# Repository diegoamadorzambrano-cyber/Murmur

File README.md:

# Murmur
An AI powered device that holds recording as your second brain.

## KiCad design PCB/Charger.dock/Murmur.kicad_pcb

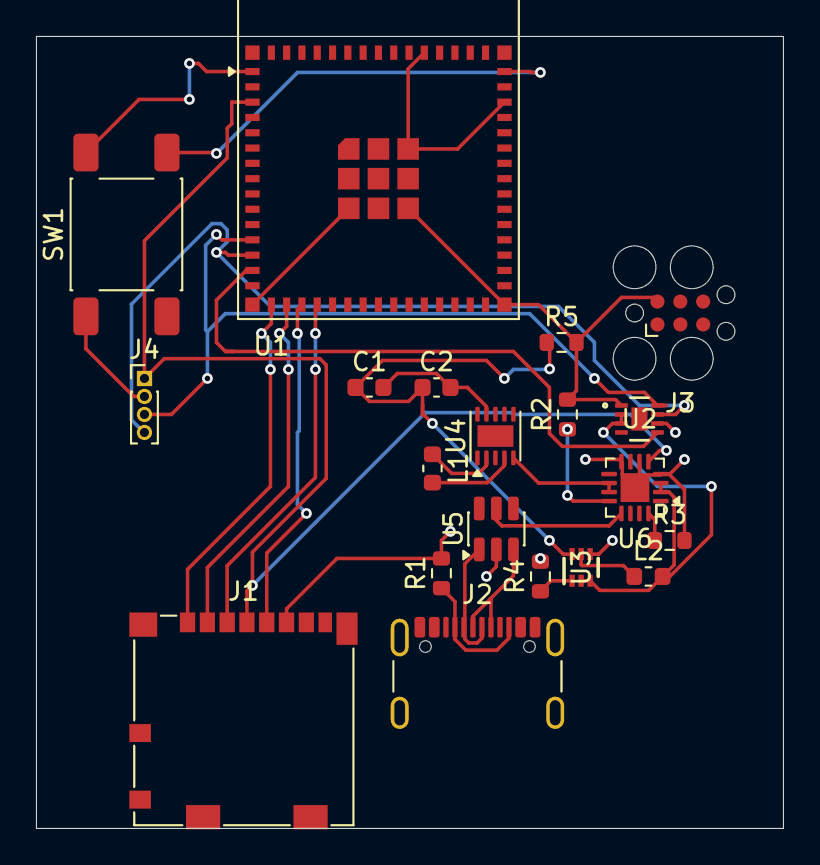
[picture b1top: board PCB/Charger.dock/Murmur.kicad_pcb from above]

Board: 2 copper layers, 41.5 x 44.0 mm, 20 parts (0 on the bottom side), 25 nets.

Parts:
C1, C2: 22nf; C_0603_1608Metric
J1: Molex 104031-0811; microSD_HC_Molex_104031-0811
J2: USB4105-GF-A; USB_C_Receptacle_GCT_USB4105-xx-A_16P_TopMnt_Horizontal
J3: Conn_01x04_Pin; Tag-Connect_TC2030-IDC-FP_2x03_P1.27mm_Vertical
J4: I2C OLED; PinHeader_1x04_P1.00mm_Vertical
L1: 1.5nh; L_0603_1608Metric
L2: 1nh; L_0603_1608Metric
R1: 5.1kOhm; R_0603_1608Metric
R2: 1.5kOhm; R_0603_1608Metric
R3: 1.78kOhm; R_0603_1608Metric
R4: 100kOhm; R_0603_1608Metric
R5: 732kOhm; R_0603_1608Metric
SW1: SW_Push; SW_Push_1P1T_NO_E-Switch_TL3301NxxxxxG
U1: ESP32-S3-MINI-1; ESP32-S2-MINI-1
U2: MAX17048G+T10; 21-0168E_T822-3_MXM
U3: TPS61023DRLR; DRL0006A
U4: TPS63031DSK; WSON-10-1EP_2.5x2.5mm_P0.5mm_EP1.2x2mm
U5: USBLC6-2SC6; SOT-23-6
U6: BQ24074RGT; VQFN-16-1EP_3x3mm_P0.5mm_EP1.6x1.6mm

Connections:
+3.3V: J1.4 (VDD), J4.1, U1.3 (3V3), U4.1 (VOUT), U4.6 (EN), U6.5 (EN2)
+5V: C1.1, C2.1, R5.1, U3.6 (VOUT)
+BATT: L2.2, U2.2 (CELL), U2.3 (VDD), U3.2 (EN), U3.3 (VIN), U6.2 (BAT), U6.3 (BAT)
-BATT: C1.2, C2.2, J1.6 (VSS), J3.2, J4.2, R1.2, R2.2, R3.2, R4.2, R5.2, SW1.1, U1.1 (GND), U1.2 (GND), U1.42 (GND), U1.43 (GND), U1.46 (GND), U1.47 (GND), U1.48 (GND), U1.49 (GND), U1.50 (GND), U1.51 (GND), U1.52 (GND), U1.53 (GND), U1.54 (GND), U1.55 (GND), U1.56 (GND), U1.57 (GND), U1.58 (GND), U1.59 (GND), U1.60 (GND), U1.61 (GND), U1.62 (GND), U1.63 (GND), U1.64 (GND), U1.65 (GND), U2.1 (CTG), U2.4 (GND), U2.6 (QSTRT), U3.4 (GND), U4.7 (PS/SYNC), U4.9 (GND), U5.2 (GND), U6.4 (~CE), U6.6 (EN1), U6.8 (VSS), U6.17 (VSS)
/CC: J2.A5 (CC1), J2.B5 (CC2), R1.1
/DN: J2.A7 (DN1), J2.B7 (DN2), U5.1 (I/O1)
/DP: J2.A6 (DP1), J2.B6 (DP2), U5.3 (I/O2)
/ILIM: R2.1, U6.12 (ILIM)
/IO8: J4.3, U1.12 (IO8), U2.8 (SDA)
/IO9: J4.4, U1.13 (IO9), U2.7 (SCL)
/IO10: U1.6 (IO2), U1.14 (IO10), U2.5 (*ALRT)
/IO12: J1.1 (DAT2), U1.16 (IO12)
/IO13: J1.2 (CD/DAT3), U1.17 (IO13)
/IO14: J1.5 (CLK), U1.18 (IO14)
/IO15: J1.3 (CMD), U1.19 (IO15)
/IO19: U1.39 (TXD0), U5.4 (I/O2)
/IO20: U1.40 (RXD0), U5.6 (I/O1)
/ISET: R3.1, U6.16 (ISET)
/OUT: U4.5 (VIN), U6.10 (OUT), U6.11 (OUT)
/VBUS: U5.5 (VBUS), U6.13 (IN)
unnamed: SW1.2, U1.45 (EN)
unnamed: R4.1, U3.1 (FB)
unnamed: L2.1, U3.5 (SW)
unnamed: L1.2, U4.4 (L1)
unnamed: L1.1, U4.2 (L2)

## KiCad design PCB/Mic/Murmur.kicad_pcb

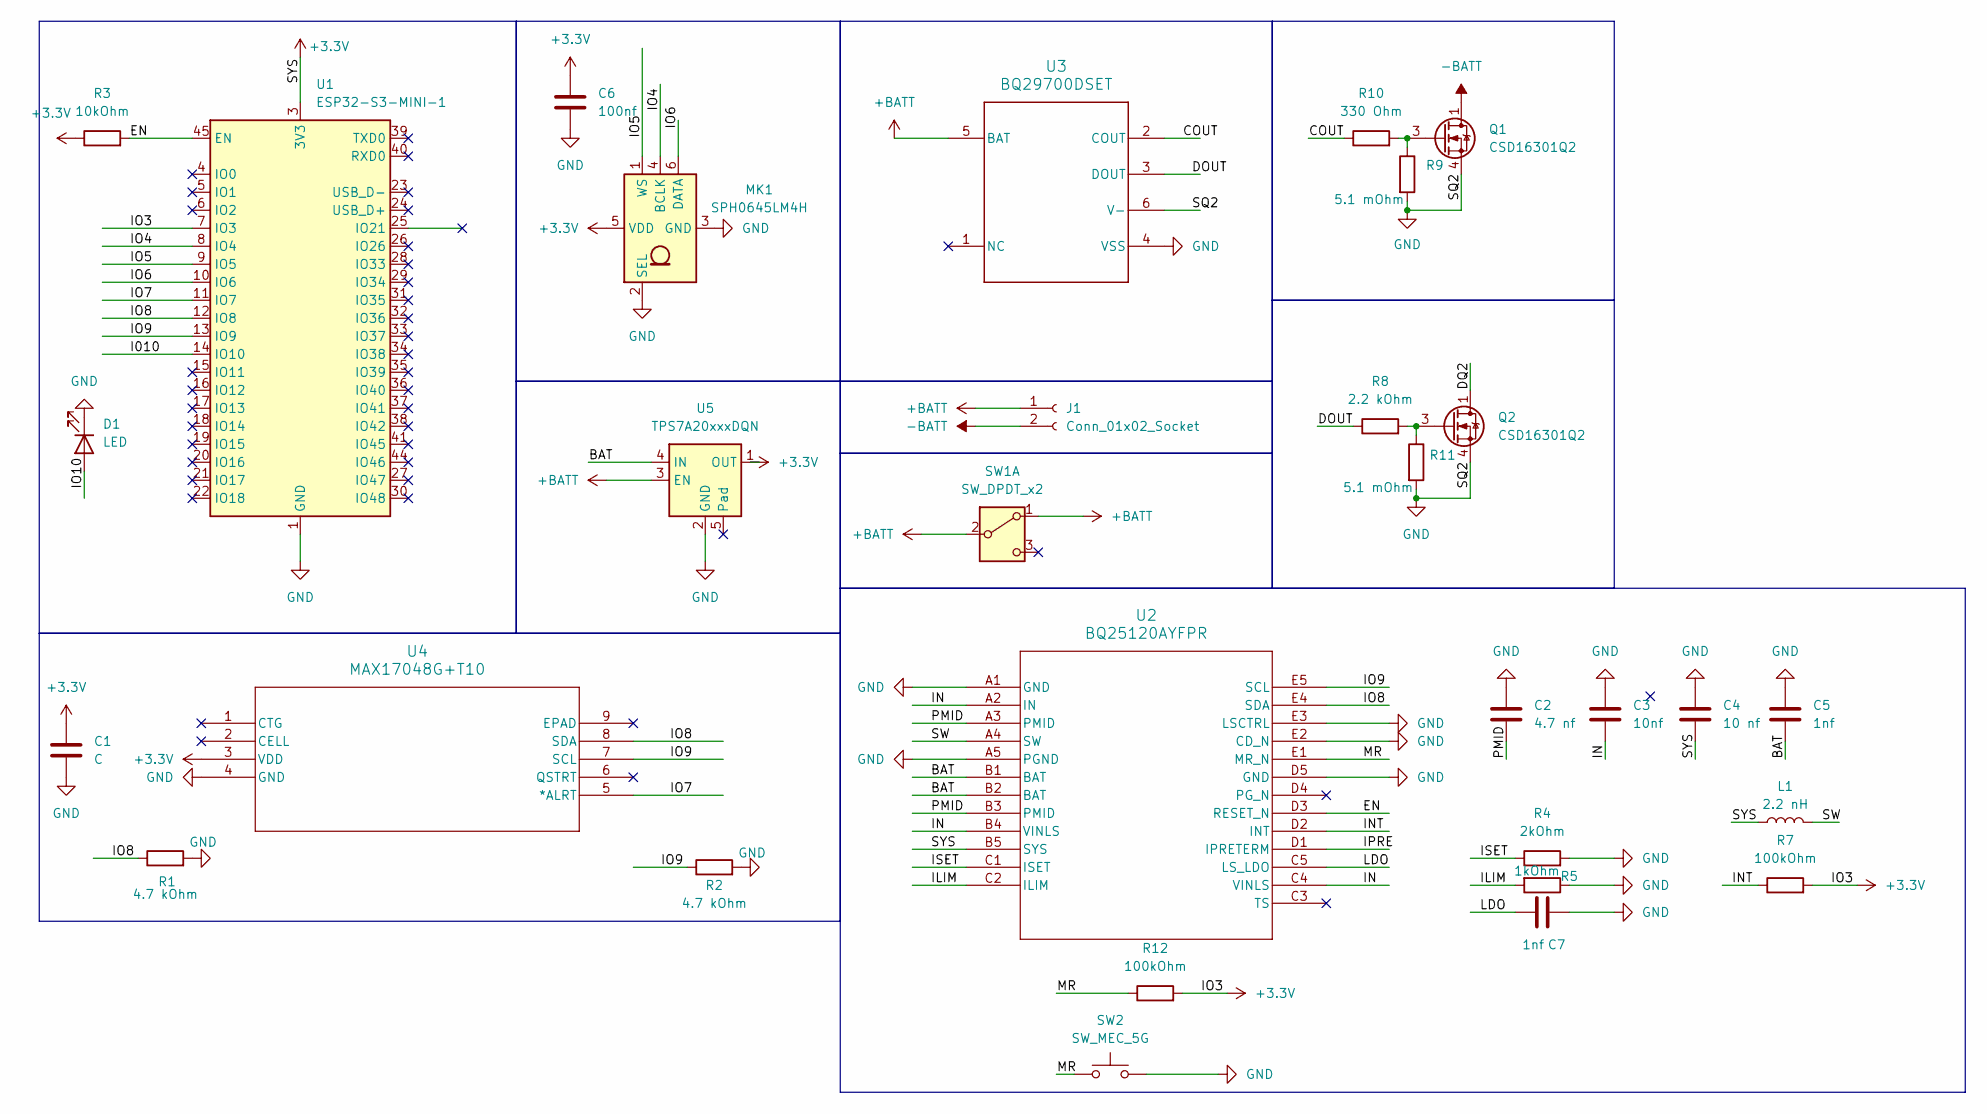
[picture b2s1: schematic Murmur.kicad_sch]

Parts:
C1: C; C_0603_1608Metric
C2: 4.7 nf; C_0603_1608Metric
C3: 10nf; C_0603_1608Metric
C4: 10 nf; C_0603_1608Metric
C5, C7: 1nf; C_0603_1608Metric
C6: 100nf; C_0603_1608Metric
D1: LED; Texas_DQK
J1: Conn_01x02_Socket; Tag-Connect_TC2030-IDC-FP_2x03_P1.27mm_Vertical
L1: 2.2 nH; L_0402_1005Metric
MK1: SPH0645LM4H; Knowles_SPH0645LM4H-6_3.5x2.65mm
Q1, Q2: CSD16301Q2; Texas_DQK
R1, R2: 4.7 kOhm; R_0603_1608Metric
R3: 10kOhm; R_0603_1608Metric
R4: 2kOhm; R_0603_1608Metric
R5: 1kOhm; R_0603_1608Metric
R7, R12: 100kOhm; R_0603_1608Metric
R8: 2.2 kOhm; R_0603_1608Metric
R9, R11: 5.1 mOhm; R_0603_1608Metric
R10: 330 Ohm; R_0603_1608Metric
SW1: SW_DPDT_x2; SW_PUSH_1P1T_6x3.5mm_H5.0_APEM_MJTP1250
SW2: SW_MEC_5G; SW_Push_SPST_NO_Alps_SKRK
U1: ESP32-S3-MINI-1; ESP32-S2-MINI-1
U2: BQ25120AYFPR; YFP0025BABD_TEX
U3: BQ29700DSET; DSE0006A
U4: MAX17048G+T10; 21-0168E_T822-3_MXM
U5: TPS7A20xxxDQN; Texas_X2SON-4_1x1mm_P0.65mm

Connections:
+3.3V: C1.1, C4.2, C6.1, L1.1, MK1.5 (VDD), R3.1, R7.2, R12.2, U1.3 (3V3), U1.7 (IO3), U2.B5 (SYS), U4.3 (VDD), U5.1 (OUT)
+BATT: J1.1, SW1.1 (A), SW1.2 (B), U3.5 (BAT), U5.3 (EN)
-BATT: J1.2, Q1.1 (D), Q1.2 (D), Q1.5 (D), Q1.6 (D), Q1.8 (D)
/BAT: C5.2, U2.B1 (BAT), U2.B2 (BAT), U5.4 (IN)
/COUT: R10.1, U3.2 (COUT)
/DOUT: R8.1, U3.3 (DOUT)
/DQ2: Q2.1 (D), Q2.2 (D), Q2.5 (D), Q2.6 (D), Q2.8 (D)
/EN: R3.2, U1.45 (EN), U2.D3 (RESET_N)
/I010: U1.14 (IO10)
/ILIM: R5.2, U2.C2 (ILIM)
/IN: C3.2, U2.A2 (IN), U2.B4 (VINLS), U2.C4 (VINLS)
/INT: R7.1, U2.D2 (INT)
/IO4: MK1.4 (BCLK), U1.8 (IO4)
/IO5: MK1.1 (WS), U1.9 (IO5)
/IO6: MK1.6 (DATA), U1.10 (IO6)
/IO7: U1.11 (IO7), U4.5 (*ALRT)
/IO8: R1.1, U1.12 (IO8), U2.E4 (SDA), U4.8 (SDA)
/IO9: R2.1, U1.13 (IO9), U2.E5 (SCL), U4.7 (SCL)
/IO10: D1.2 (A)
/IPRE: U2.D1 (IPRETERM)
/ISET: R4.1, U2.C1 (ISET)
/LDO: C7.1, U2.C5 (LS_LDO)
/MR: R12.1, SW2.1 (A), SW2.2 (A), U2.E1 (MR_N)
/PMID: C2.2, U2.A3 (PMID), U2.B3 (PMID)
/SW: L1.2, U2.A4 (SW)
GND: C1.2, C2.1, C3.1, C4.1, C5.1, C6.2, C7.2, D1.1 (K), MK1.2 (SEL), MK1.3 (GND), Q1.4 (S), Q1.7 (S), Q2.4 (S), Q2.7 (S), R1.2, R2.2, R4.2, R5.1, R9.2, R11.2, SW2.3 (B), SW2.4 (B), U1.1 (GND), U1.2 (GND), U1.42 (GND), U1.43 (GND), U1.46 (GND), U1.47 (GND), U1.48 (GND), U1.49 (GND), U1.50 (GND), U1.51 (GND), U1.52 (GND), U1.53 (GND), U1.54 (GND), U1.55 (GND), U1.56 (GND), U1.57 (GND), U1.58 (GND), U1.59 (GND), U1.60 (GND), U1.61 (GND), U1.62 (GND), U1.63 (GND), U1.64 (GND), U1.65 (GND), U2.A1 (GND), U2.A5 (PGND), U2.D5 (GND), U2.E2 (CD_N), U2.E3 (LSCTRL), U3.4 (VSS), U3.6 (V-), U4.4 (GND), U5.2 (GND)
unnamed: Q1.3 (G), R9.1, R10.2
unnamed: Q2.3 (G), R8.2, R11.1

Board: 2 copper layers, 31 parts (0 on the bottom side), 25 nets, no tracks yet.
